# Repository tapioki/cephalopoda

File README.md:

# Cephalopoda

A collection of low profile split ergonomic mechanical keyboards I have created using [Ergogen](https://github.com/mrzealot/ergogen).

## Sepia officinalis

AKA S. officinalis, S.O., "Cuttlefish"

34 keys, aggresive pinky stagger with top row omitted.

## Metasepia pfefferi

AKA M. pfefferi, M.P., "Flamboyant cuttlefish"

26 keys, similar to the S. officinalis, but with top/bottom keys of pinky and inner columns omitted. 2 thumb keys.

## Dosidicus gigas

AKA D. gigas, D.G., "Jumbo squid"

32 keys, same pinky stagger as S. officinalis and M. pfefferi, but with all "alpha" keys included. Pinky, ring, index, and inner columns splayed at 15, 5, -5, -5 degrees from middle column.

## Todarodes pacificus

AKA T. pacificus, T.P., "Japanese flying squid"

30 keys, 15, 5, 0, -5, -5 degree splay. My take on the Hummingbird layout.

## Todarodes sagittatus

AKA T. sagittatus, T.S., "European flying squid"

Same stagger as the T. pacificus, but no splay.

## Idiosepius thailandicus

AKA I. thailandicus, I.T., "Pygmy bobtail squid"

Designed with the ARTSEY layout in mind, but could also be used with ASTENIOP.
BlueMicro compatible.

---

Thank you [@o.bijmarie](https://instagram.com/o.bijmarie) for the photos of the Sepia officinalis, perce for logo help, and everyone on the Absolem club discord for their support.

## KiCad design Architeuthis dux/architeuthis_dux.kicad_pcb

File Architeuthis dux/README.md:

# Architeuthis dux

AKA A. dux, A.D., "Giant squid"

34 keys, same stagger as D. gigas, but with two thumb keys included. Pinky, ring, index, and inner columns splayed at 15, 5, 0, -5, -5 degrees.

SplitKB Tenting puck support.

Thank you perce for the logo

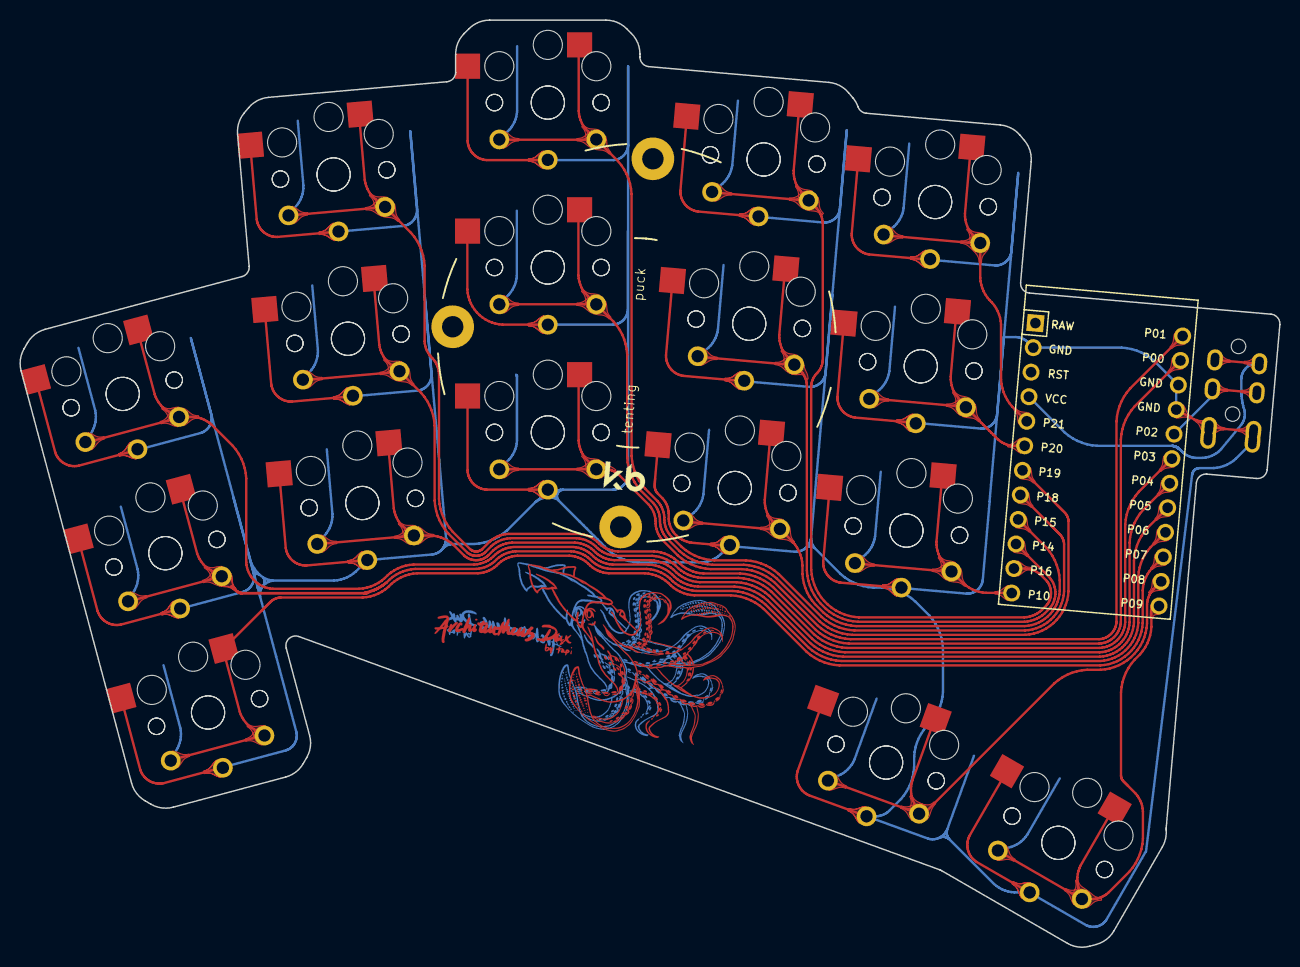
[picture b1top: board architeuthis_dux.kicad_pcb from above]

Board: 2 copper layers, 129.9 x 95.6 mm, 36 parts (0 on the bottom side), 20 nets.

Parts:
C1: ProMicro
S1, S2, S3, S4, S5, S6, S7, S8, S9, S10, S11, S12, S13, S14, S15, S16, S17, S18, S19, S20, S21, S22, S23, S24, S25, S26, S27, S28, S29, S30, S31, S32, S33, S34: PG1350
T1: TRRS-PJ-320A-dual

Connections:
GND: C1.2, C1.15, C1.16, S1.2, S2.2, S3.2, S4.2, S5.2, S6.2, S7.2, S8.2, S9.2, S10.2, S11.2, S12.2, S13.2, S14.2, S15.2, S16.2, S17.2, S18.2, S19.2, S20.2, S21.2, S22.2, S23.2, S24.2, S25.2, S26.2, S27.2, S28.2, S29.2, S30.2, S31.2, S32.2, S33.2, S34.2, T1.1, T1.2
P0: C1.14, S11.1, S12.1
P1: C1.13, S13.1, S14.1
P2: C1.17, T1.3
P3: C1.18, S9.1, S10.1
P4: C1.19, S7.1, S8.1
P5: C1.20, S5.1, S6.1
P6: C1.21, S3.1, S4.1
P7: C1.22, S1.1, S2.1
P8: C1.23, S31.1, S32.1
P9: C1.24, S33.1, S34.1
P10: C1.12, S25.1, S26.1
P14: C1.10, S21.1, S22.1
P15: C1.9, S19.1, S20.1
P16: C1.11, S23.1, S24.1
P18: C1.8, S17.1, S18.1
P19: C1.7, S15.1, S16.1
P20: C1.6, S27.1, S28.1
P21: C1.5, S29.1, S30.1
VCC: C1.4, T1.4

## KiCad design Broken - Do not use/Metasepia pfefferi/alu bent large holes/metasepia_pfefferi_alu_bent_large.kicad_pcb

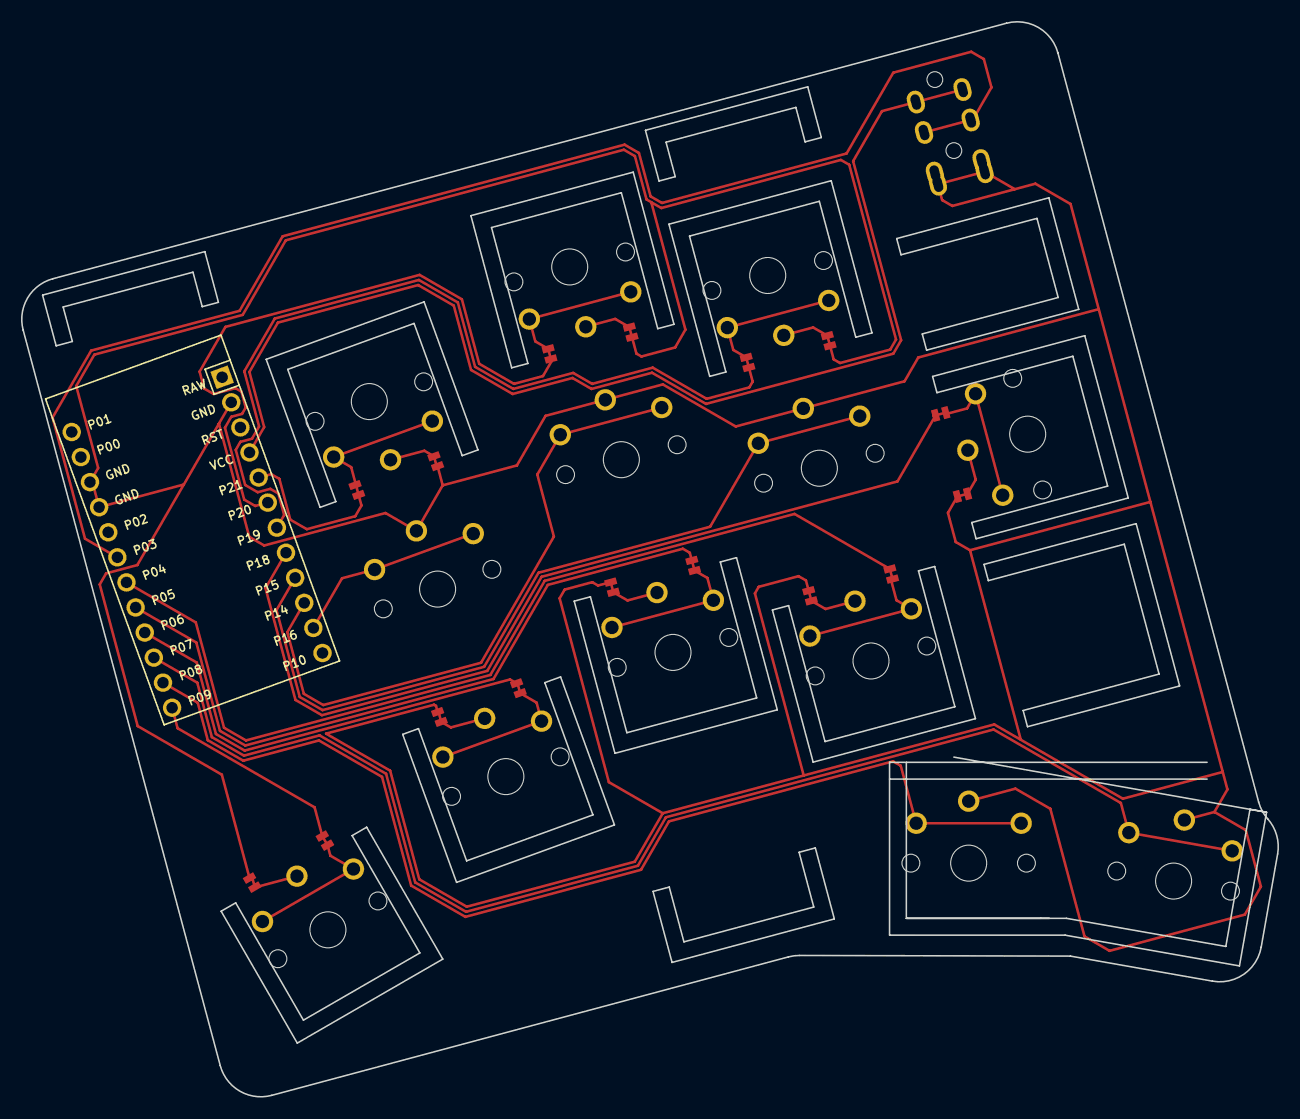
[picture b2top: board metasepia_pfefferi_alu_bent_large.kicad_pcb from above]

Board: 2 copper layers, 119.6 x 102.4 mm, 30 parts (0 on the bottom side), 14 nets.

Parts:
C1: ProMicro
J1, J2, J3, J4, J5, J6, J7, J8, J9, J10, J11, J12, J13, J14, J15, J16: Jumper
S1, S2, S3, S4, S5, S6, S7, S8, S9, S10, S11, S12, S13: PG1350

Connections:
GND: C1.2, C1.15, C1.16, J1.1, J1.2, J3.1, J3.2, J5.1, J5.2, J7.1, J7.2, J9.1, J9.2, J11.1, J11.2, J13.1, J13.2, J15.1, J15.2, S1.2, S2.2, S3.2, S4.2, S5.2, S6.2, S7.2, S8.2, S9.2, S10.2, S11.2, S12.2, S13.2
P4: C1.19, J12.1, J12.2, S8.1
P5: C1.20, J8.1, J8.2, S5.1
P6: C1.21, J4.1, J4.2, S2.1
P7: C1.22, S13.1
P8: C1.23, S12.1
P9: C1.24, J2.1, J2.2, S1.1
P14: C1.10, S6.1
P15: C1.9, S9.1
P16: C1.11, S3.1
P18: C1.8, J16.1, J16.2, S11.1
P19: C1.7, J14.1, J14.2, S10.1
P20: C1.6, J10.1, J10.2, S7.1
P21: C1.5, J6.1, J6.2, S4.1

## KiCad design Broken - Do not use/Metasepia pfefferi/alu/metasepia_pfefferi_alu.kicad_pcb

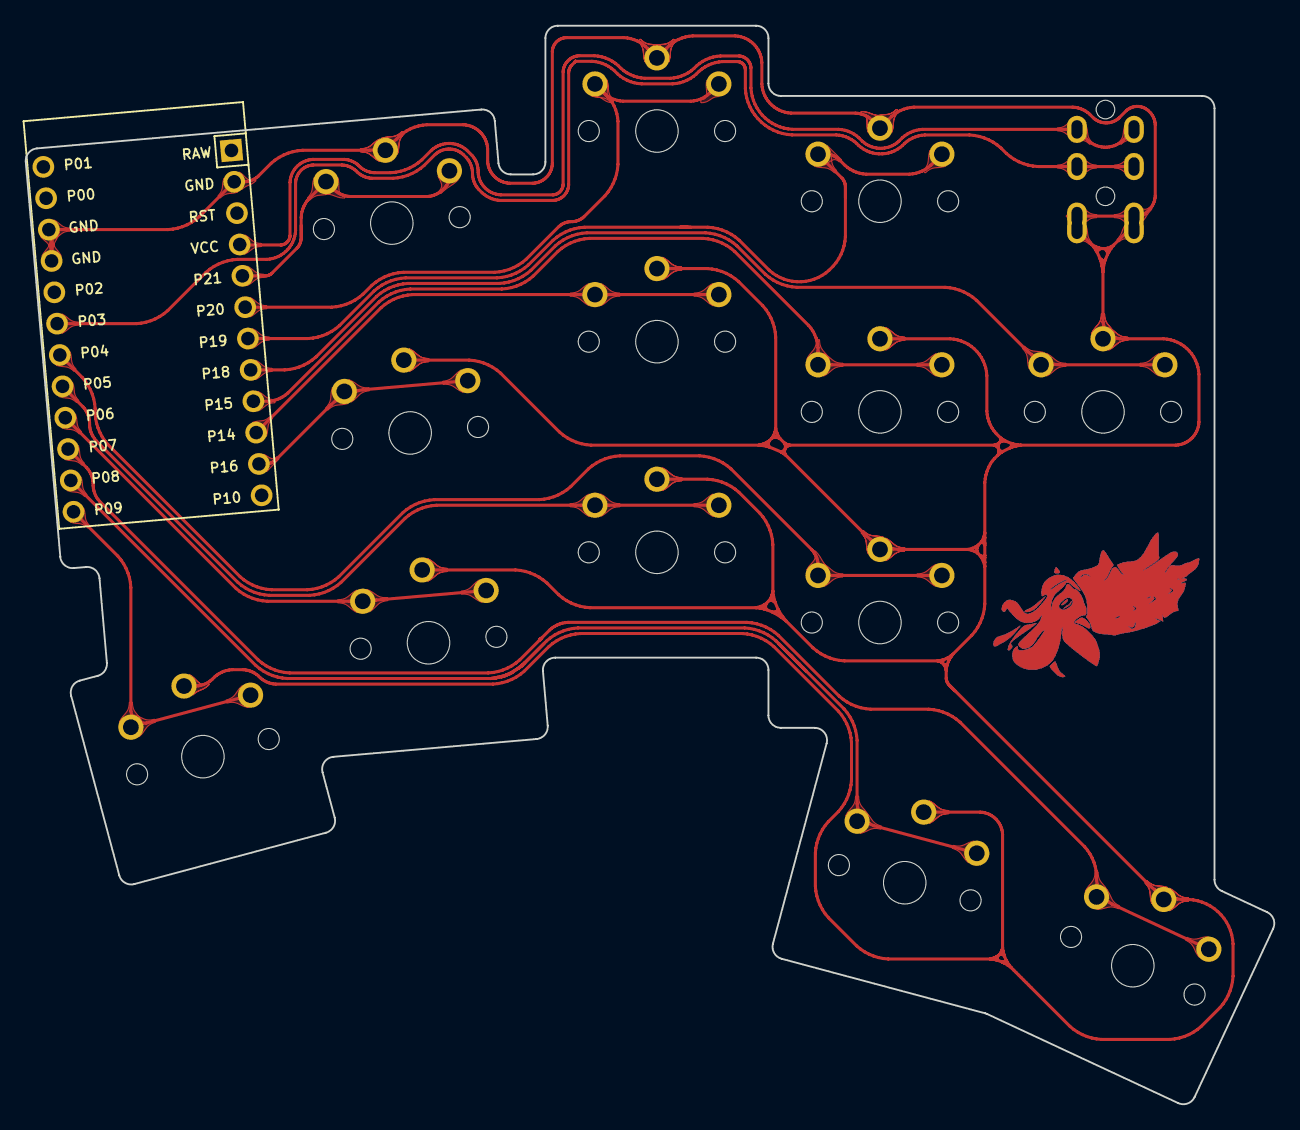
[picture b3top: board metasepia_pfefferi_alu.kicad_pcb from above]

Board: 2 copper layers, 100.8 x 87.0 mm, 14 parts (0 on the bottom side), 14 nets.

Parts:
C1: ProMicro
S1, S2, S3, S4, S5, S6, S7, S8, S9, S10, S11, S12, S13: PG1350

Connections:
GND: C1.2, C1.15, C1.16, S1.2, S2.2, S3.2, S4.2, S5.2, S6.2, S7.2, S8.2, S9.2, S10.2, S11.2, S12.2, S13.2
P4: C1.19, S8.1
P5: C1.20, S5.1
P6: C1.21, S2.1
P7: C1.22, S13.1
P8: C1.23, S12.1
P9: C1.24, S1.1
P14: C1.10, S6.1
P15: C1.9, S9.1
P16: C1.11, S3.1
P18: C1.8, S11.1
P19: C1.7, S10.1
P20: C1.6, S7.1
P21: C1.5, S4.1

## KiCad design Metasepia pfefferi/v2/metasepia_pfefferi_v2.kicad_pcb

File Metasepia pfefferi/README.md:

# Metasepia pfefferi
    IN PROGRESS

AKA M. pfefferi, M.P., "The second one", "Flamboyant cuttlefish"

26 keys, similar to the S. officinalis, but with top/bottom keys of pinky and inner columns omitted. 2 thumb keys.

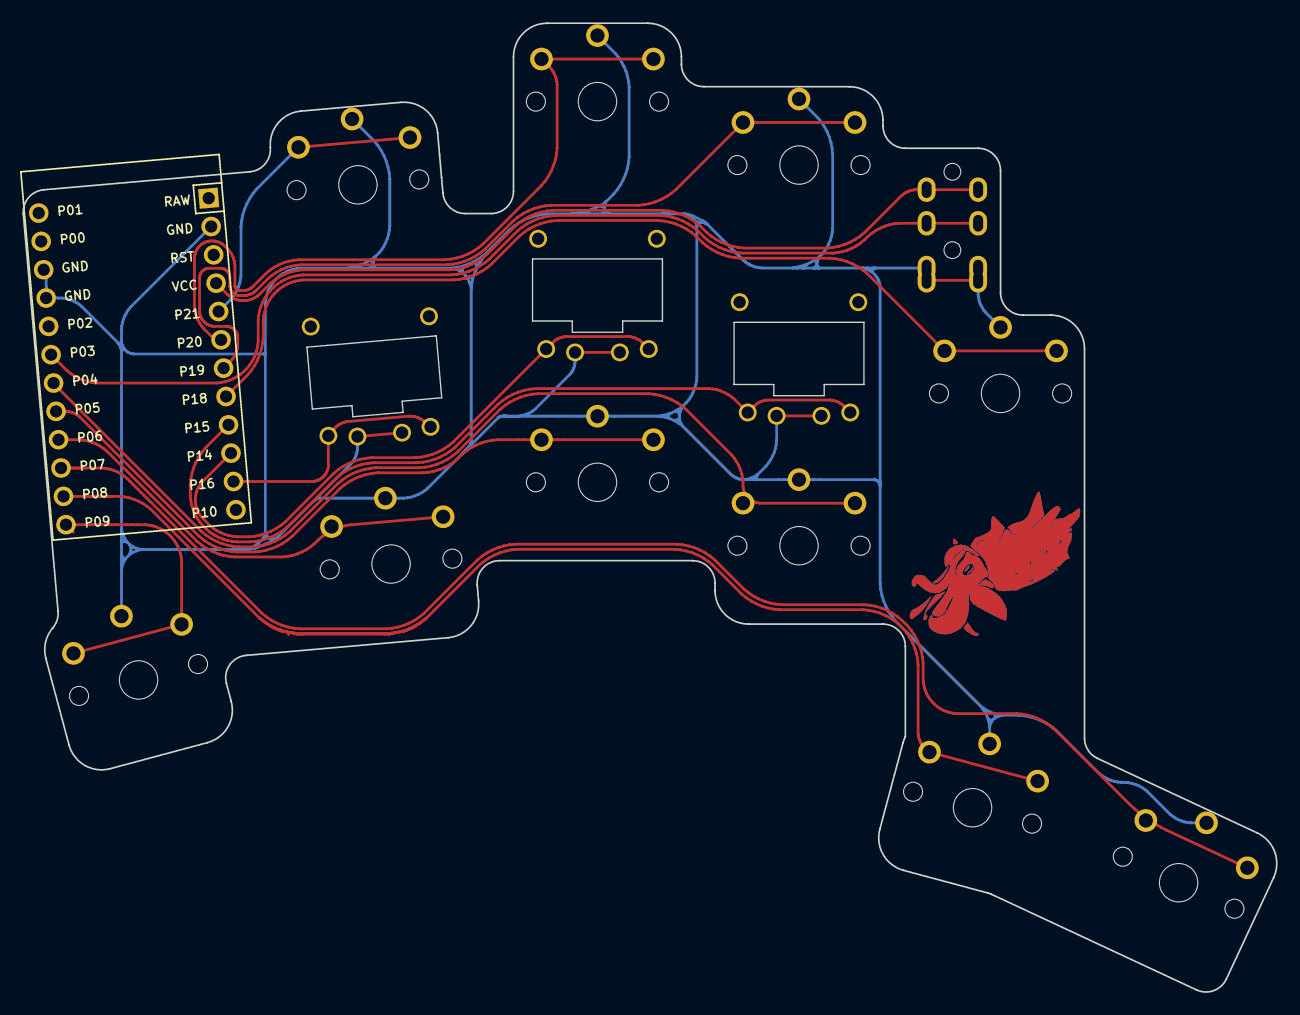
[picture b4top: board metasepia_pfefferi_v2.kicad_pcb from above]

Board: 2 copper layers, 112.0 x 86.5 mm, 14 parts (0 on the bottom side), 14 nets.

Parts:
MCU1: ProMicro
S1, S2, S4, S5, S7, S8, S10, S11, S12, S13: PG1350
S3, S6, S9: Kailh_PG1232

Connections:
GND: MCU1.2, MCU1.15, MCU1.16, S1.2, S2.2, S3.2, S4.2, S5.2, S6.2, S7.2, S8.2, S9.2, S10.2, S11.2, S12.2, S13.2
P4: MCU1.19, S8.1
P5: MCU1.20, S5.1
P6: MCU1.21, S2.1
P7: MCU1.22, S13.1
P8: MCU1.23, S12.1
P9: MCU1.24, S1.1
P14: MCU1.10, S6.1
P15: MCU1.9, S9.1
P16: MCU1.11, S3.1
P18: MCU1.8, S11.1
P19: MCU1.7, S10.1
P20: MCU1.6, S7.1
P21: MCU1.5, S4.1

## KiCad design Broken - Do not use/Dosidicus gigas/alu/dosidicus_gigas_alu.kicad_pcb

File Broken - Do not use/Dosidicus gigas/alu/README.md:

Aluminum boards are not reversible. This board will not work. DO NOT ORDER THIS BOARD UNLESS YOU WANT AN EXPENSIVE COASTER.

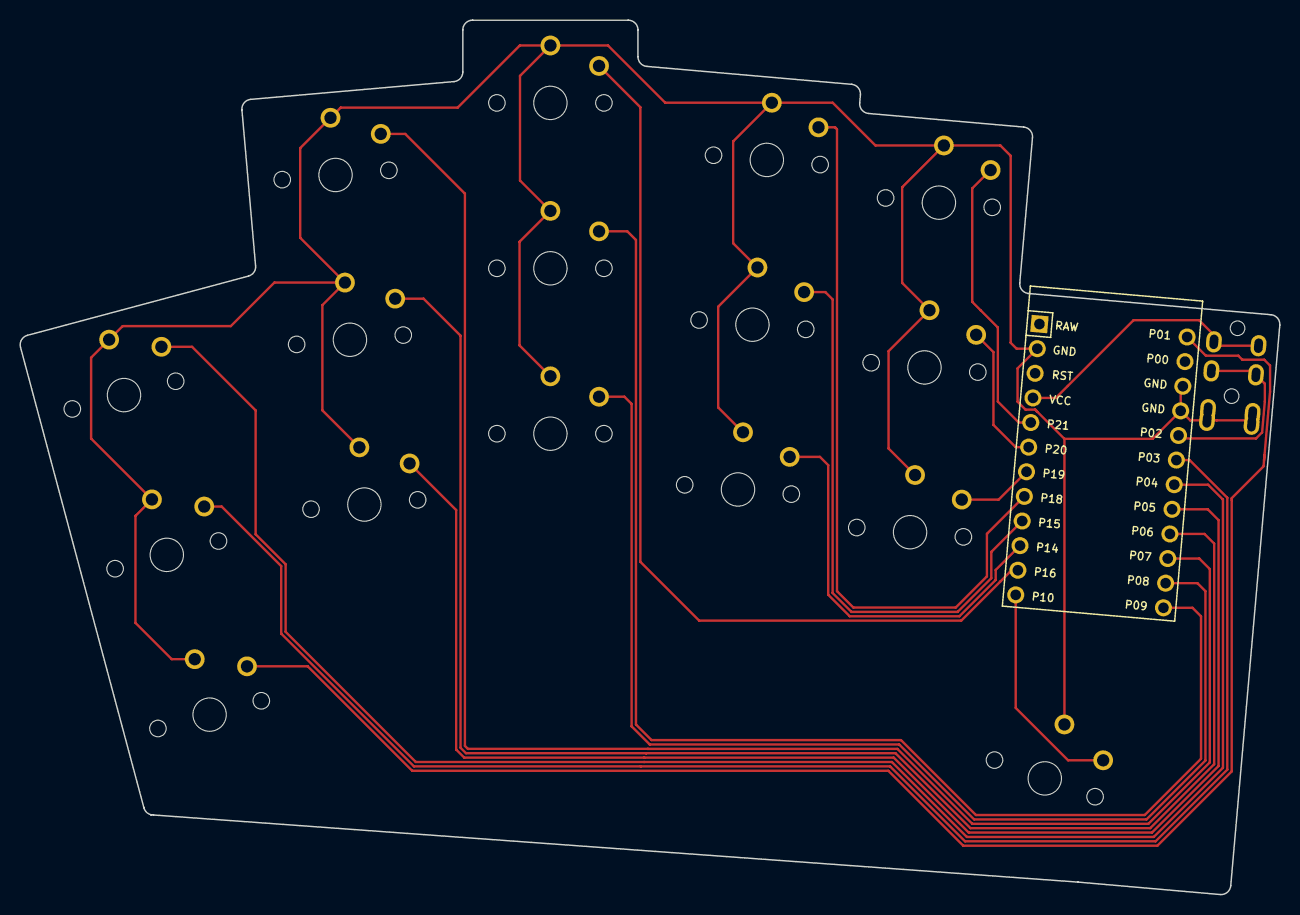
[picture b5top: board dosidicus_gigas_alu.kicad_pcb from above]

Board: 2 copper layers, 129.5 x 89.9 mm, 17 parts (0 on the bottom side), 17 nets.

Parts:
C1: ProMicro
S1, S2, S3, S4, S5, S6, S7, S8, S9, S10, S11, S12, S13, S14, S15, S16: PG1350

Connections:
GND: C1.2, C1.15, C1.16, S1.2, S2.2, S3.2, S4.2, S5.2, S6.2, S7.2, S8.2, S9.2, S10.2, S11.2, S12.2, S13.2, S14.2, S15.2, S16.2
P1: C1.13, S1.1
P3: C1.18, S2.1
P4: C1.19, S3.1
P5: C1.20, S4.1
P6: C1.21, S5.1
P7: C1.22, S6.1
P8: C1.23, S7.1
P9: C1.24, S8.1
P10: C1.12, S16.1
P14: C1.10, S10.1
P15: C1.9, S11.1
P16: C1.11, S9.1
P18: C1.8, S12.1
P19: C1.7, S13.1
P20: C1.6, S14.1
P21: C1.5, S15.1

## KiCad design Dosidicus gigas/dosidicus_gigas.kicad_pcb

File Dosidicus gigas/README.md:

# Dosidicus gigas

AKA D. gigas, D.G., "The third one", "Jumbo squid"

32 keys, same pinky stagger as S. officinalis and M. pfefferi, but with all "alpha" keys included. Pinky, ring, index, and inner columns splayed at 15, 5, -5, -5 degrees from middle column.

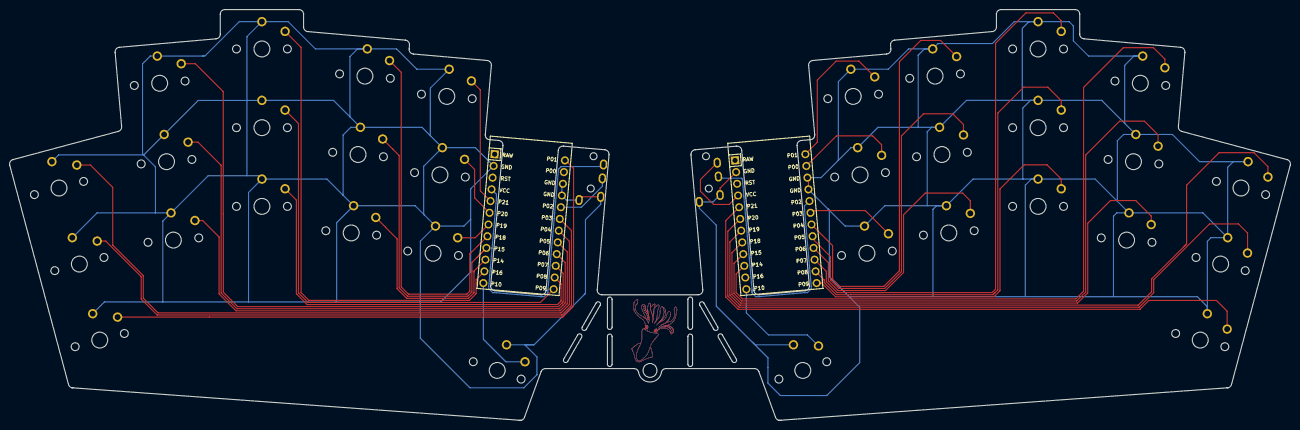
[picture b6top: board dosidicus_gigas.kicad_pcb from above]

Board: 2 copper layers, 276.6 x 88.7 mm, 40 parts (0 on the bottom side), 22 nets.

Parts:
C1, C2: ProMicro
H1, H2, H3, H4: breakaway_cutout
S1, S2, S3, S4, S5, S6, S7, S8, S9, S10, S11, S12, S13, S14, S15, S16, S17, S18, S19, S20, S21, S22, S23, S24, S25, S26, S27, S28, S29, S30, S31, S32: PG1350
T1, T2: TRRS-PJ-320A-dual

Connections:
GND: C1.2, C1.15, C1.16, C2.2, C2.15, C2.16, S1.2, S2.2, S3.2, S4.2, S5.2, S6.2, S7.2, S8.2, S9.2, S10.2, S11.2, S12.2, S13.2, S14.2, S15.2, S16.2, S17.2, S18.2, S19.2, S20.2, S21.2, S22.2, S23.2, S24.2, S25.2, S26.2, S27.2, S28.2, S29.2, S30.2, S31.2, S32.2, T1.1, T1.2, T2.1, T2.2
P0: C1.14, C2.14, S30.1
P1: C1.13, C2.13, S1.1, S31.1
P2: C1.17, C2.17, T1.3, T2.3
P3: C1.18, C2.18, S2.1, S29.1
P4: C1.19, C2.19, S3.1, S28.1
P5: C1.20, C2.20, S4.1, S27.1
P6: C1.21, C2.21, S5.1, S26.1
P7: C1.22, C2.22, S6.1, S25.1
P8: C1.23, C2.23, S7.1, S24.1
P9: C1.24, C2.24, S8.1, S23.1
P10: C1.12, C2.12, S16.1, S32.1
P14: C1.10, C2.10, S10.1, S22.1
P15: C1.9, C2.9, S11.1, S21.1
P16: C1.11, C2.11, S9.1
P18: C1.8, C2.8, S12.1, S20.1
P19: C1.7, C2.7, S13.1, S19.1
P20: C1.6, C2.6, S14.1, S18.1
P21: C1.5, C2.5, S15.1, S17.1
RAW: C1.1, C2.1
RST: C1.3, C2.3
VCC: C1.4, C2.4, T1.4, T2.4

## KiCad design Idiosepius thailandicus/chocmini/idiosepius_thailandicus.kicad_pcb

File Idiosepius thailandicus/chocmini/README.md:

# Idiosepius thailandicus

AKA I. thailandicus, I.T., "The sixth one", "Pygmy bobtail squid"

Designed with the ARTSEY layout in mind, but could also be used with ASTENIOP.
BlueMicro compatible.

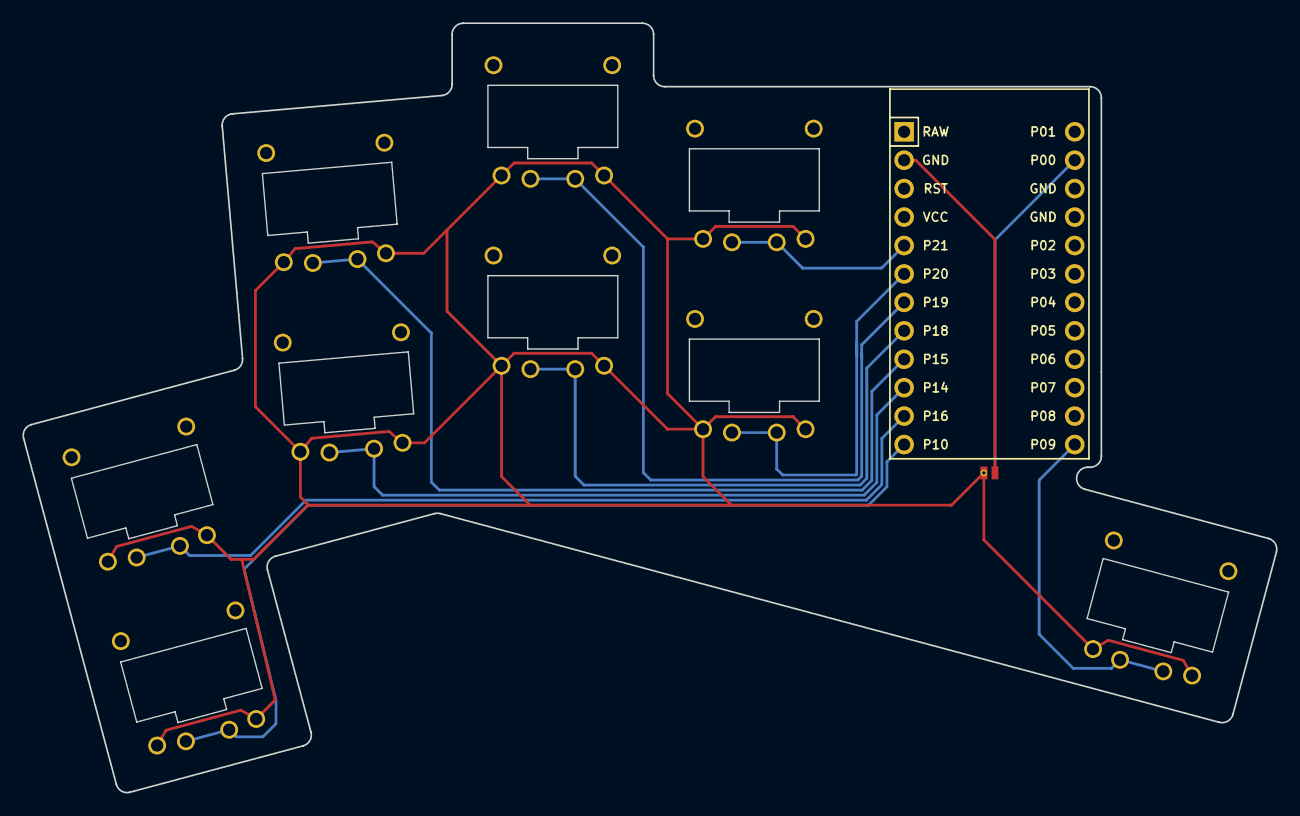
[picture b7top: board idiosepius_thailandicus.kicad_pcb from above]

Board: 2 copper layers, 112.0 x 68.7 mm, 12 parts (0 on the bottom side), 11 nets.

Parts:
C1: ProMicro
J1, J2: Jumper
S1, S2, S3, S4, S5, S6, S7, S8, S9: Kailh_PG1232

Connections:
GND: C1.2, C1.15, C1.16, J1.1, J1.2, J2.1, S1.1, S2.1, S3.1, S4.1, S5.1, S6.1, S7.1, S8.1, S9.1
P0: C1.14, J2.2
P9: C1.24, S9.2
P10: C1.12, S1.2
P14: C1.10, S3.2
P15: C1.9, S4.2
P16: C1.11, S2.2
P18: C1.8, S5.2
P19: C1.7, S6.2
P20: C1.6, S7.2
P21: C1.5, S8.2

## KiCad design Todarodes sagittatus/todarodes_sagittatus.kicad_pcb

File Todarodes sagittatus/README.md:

# Todarodes sagittatus

AKA T. sagittatus, T.S., "The fifth one", "European flying squid"

Same stagger as the T. pacificus, but no splay.

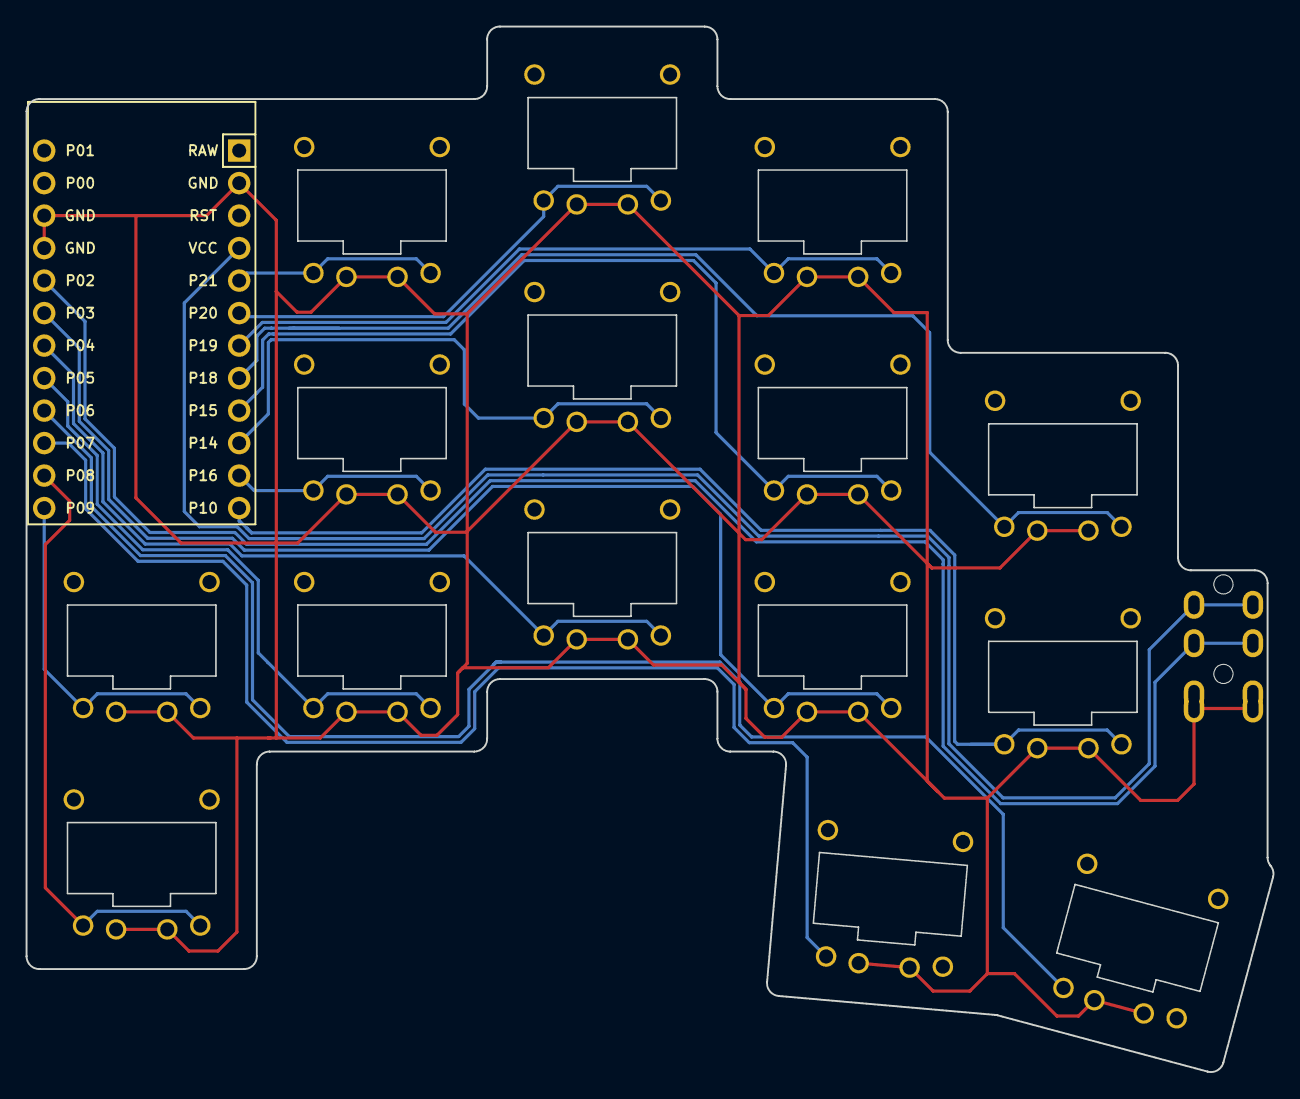
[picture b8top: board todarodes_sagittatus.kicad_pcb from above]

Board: 2 copper layers, 97.5 x 81.7 mm, 16 parts (0 on the bottom side), 16 nets.

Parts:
C1: ProMicro
S1, S2, S3, S4, S5, S6, S7, S8, S9, S10, S11, S12, S13, S14, S15: Kailh_PG1232

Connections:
GND: C1.2, C1.15, C1.16, S1.2, S2.2, S3.2, S4.2, S5.2, S6.2, S7.2, S8.2, S9.2, S10.2, S11.2, S12.2, S13.2, S14.2, S15.2
P3: C1.18, S9.1
P4: C1.19, S6.1
P5: C1.20, S3.1
P6: C1.21, S15.1
P7: C1.22, S14.1
P8: C1.23, S1.1
P9: C1.24, S2.1
P10: C1.12, S12.1
P14: C1.10, S7.1
P15: C1.9, S10.1
P16: C1.11, S4.1
P18: C1.8, S13.1
P19: C1.7, S11.1
P20: C1.6, S8.1
P21: C1.5, S5.1

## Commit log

2021-04-26 Add ergogen config
    YAML config for ergogen
2021-04-26 Add gerber files
2021-04-26 Create test
2021-04-26 Rename sepia-B_Cu.gbr to gerbers/sepia-B_Cu.gbr
2021-04-26 Rename sepia-B_Mask.gbr to gerbers/sepia-B_Mask.gbr
2021-04-26 Rename sepia-B_Paste.gbr to gerbers/sepia-B_Paste.gbr
2021-04-26 Rename sepia-B_SilkS.gbr to gerbers/sepia-B_SilkS.gbr
2021-04-26 Rename sepia-Edge_Cuts.gbr to gerbers/sepia-Edge_Cuts.gbr
2021-04-26 Rename sepia-F_Cu.gbr to gerbers/sepia-F_Cu.gbr
2021-04-26 Rename sepia-F_Paste.gbr to gerbers/sepia-F_Paste.gbr
2021-04-26 Rename sepia-F_SilkS.gbr to gerbers/sepia-F_SilkS.gbr
2021-04-26 Rename sepia-job.gbrjob to gerbers/sepia-job.gbrjob
2021-04-26 Rename sepia.drl to gerbers/sepia.drl
2021-04-26 Rename sepia-F_Mask.gbr to gerbers/sepia-F_Mask.gbr
2021-04-26 Changed direction of the cuttlefish
2021-06-29 Added new boards
2021-06-29 Added gerbers for M. pfefferi, T. pacificus, T. sagittatus
2021-06-29 Update image
2021-06-29 Fixed folder names
2021-06-29 Fixed I. thailandicus choc/chocmini folders
2021-06-30 Added gerbers for D. gigas
2021-06-30 Changed D. gigas image
2021-07-01 Added aluminum pcb version of D. gigas
2021-07-05 Added new boards and images
2021-07-06 Added tenting puck support to A. dux
2021-07-06 Fixed routing artifact
2021-07-07 Updated logo and fixed routing
2021-07-07 Cleaned up old files
2021-07-07 Fixed text on back side
2021-07-08 release-action
2021-07-15 New image and update README
2021-08-06 Added .gitignore
2021-08-06 Added images to main readme and updated text
2021-08-06 Fixed typo in readme
2021-08-06 Added new images
2021-08-06 Moved broken pcbs to new folder, added M. pfefferi v2
2021-08-06 Fixed typo
2021-08-06 Increased font size
2021-09-04 Added case for the Architeuthis dux
2021-09-04 Fix case collison
2021-09-08 updated to add a 32 key version of the plate so you can use the extra pin if you like (for instance, for RGB strip
2021-09-30 Remove phantom drill holes on pinkie edge
2021-11-13 Fixed image links in readme.md
    The markdown was not generated correctly in github. It is case sensitive.
2023-11-07 Fixed links to Images
